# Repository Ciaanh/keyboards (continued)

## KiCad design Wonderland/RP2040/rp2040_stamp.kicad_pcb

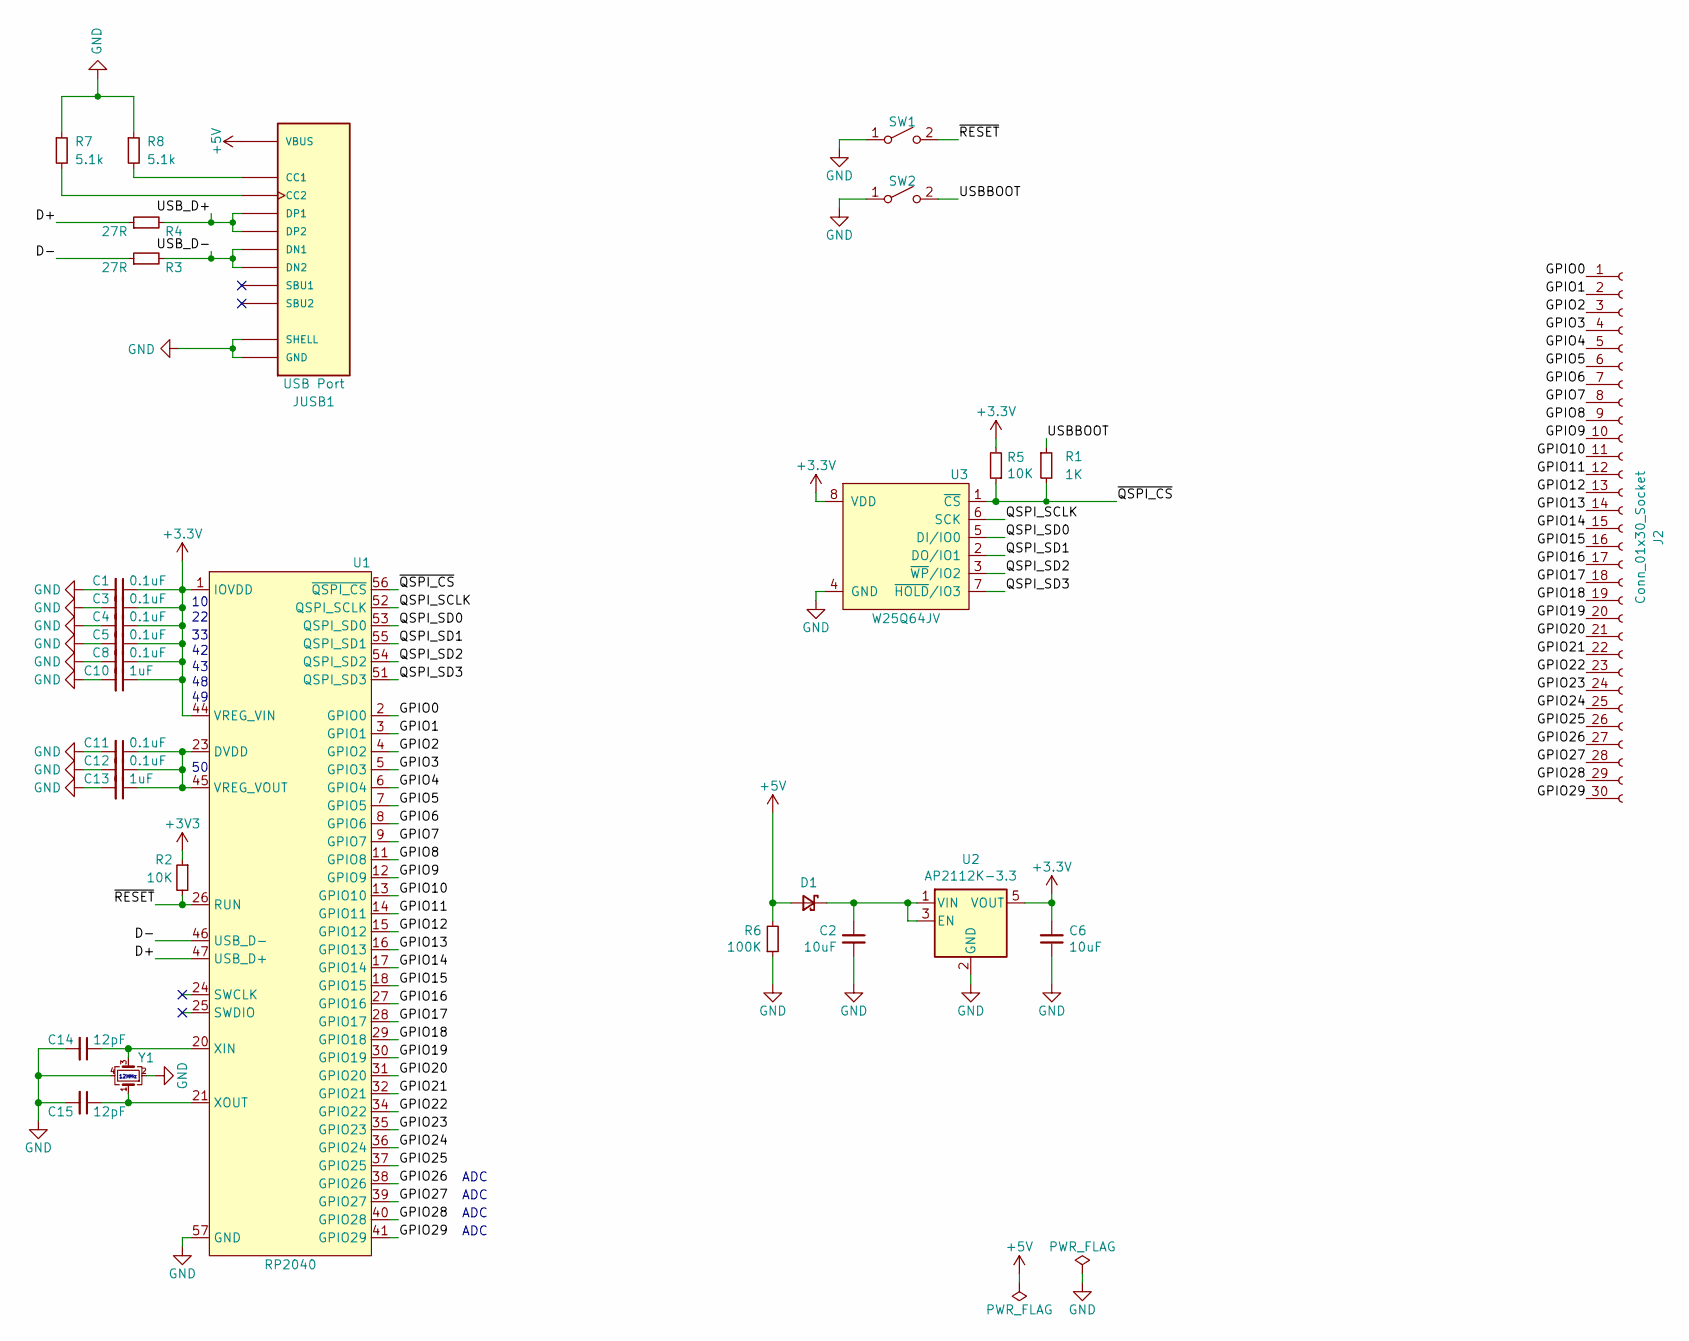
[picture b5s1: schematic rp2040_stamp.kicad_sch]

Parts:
C1, C3, C4, C5, C8, C11, C12: 0.1uF; C_0603_1608Metric
C2, C6: 10uF; C_0603_1608Metric
C10, C13: 1uF; C_0603_1608Metric
C14, C15: 12pF; C_0603_1608Metric
D1: D_Schottky_Small; D_SOD-323; LCSC C114023
J2: Conn_01x30_Socket; PinHeader_1x30_P2.54mm_Vertical
JUSB1: USB Port; GCT_USB4085-GF-A_REVA4; PARTREV A4
R1: 1K; R_0603_1608Metric
R2, R5: 10K; R_0603_1608Metric
R3, R4: 27R; R_0603_1608Metric
R6: 100K; R_0603_1608Metric
R7, R8: 5.1k; R_0603_1608Metric
SW1, SW2: SW_RESET; SW_SPST_B3U-1000P
U1: RP2040; QFN-56_EP_7x7_Pitch0.4mm
U2: AP2112K-3.3; SOT-23-5; LCSC C51118
U3: W25Q64JV; WSON-8-1EP_6x5mm_P1.27mm_EP3.4x4mm
Y1: XYDBPCNANF-12MHZ; Crystal_SMD_2520-4Pin_2.5x2.0mm; LCSC C521567

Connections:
+5V: D1.2 (A), JUSB1.A4 (VBUS), JUSB1.A9 (VBUS), JUSB1.B4 (VBUS), JUSB1.B9 (VBUS), R6.2
/D+: R4.1, U1.47 (USB_D+)
/D-: R3.1, U1.46 (USB_D-)
/GPIO0: J2.1, U1.2 (GPIO0)
/GPIO1: J2.2, U1.3 (GPIO1)
/GPIO2: J2.3, U1.4 (GPIO2)
/GPIO3: J2.4, U1.5 (GPIO3)
/GPIO4: J2.5, U1.6 (GPIO4)
/GPIO5: J2.6, U1.7 (GPIO5)
/GPIO6: J2.7, U1.8 (GPIO6)
/GPIO7: J2.8, U1.9 (GPIO7)
/GPIO8: J2.9, U1.11 (GPIO8)
/GPIO9: J2.10, U1.12 (GPIO9)
/GPIO10: J2.11, U1.13 (GPIO10)
/GPIO11: J2.12, U1.14 (GPIO11)
/GPIO12: J2.13, U1.15 (GPIO12)
/GPIO13: J2.14, U1.16 (GPIO13)
/GPIO14: J2.15, U1.17 (GPIO14)
/GPIO15: J2.16, U1.18 (GPIO15)
/GPIO16: J2.17, U1.27 (GPIO16)
/GPIO17: J2.18, U1.28 (GPIO17)
/GPIO18: J2.19, U1.29 (GPIO18)
/GPIO19: J2.20, U1.30 (GPIO19)
/GPIO20: J2.21, U1.31 (GPIO20)
/GPIO21: J2.22, U1.32 (GPIO21)
/GPIO22: J2.23, U1.34 (GPIO22)
/GPIO23: J2.24, U1.35 (GPIO23)
/GPIO24: J2.25, U1.36 (GPIO24)
/GPIO25: J2.26, U1.37 (GPIO25)
/GPIO26: J2.27, U1.38 (GPIO26)
/GPIO27: J2.28, U1.39 (GPIO27)
/GPIO28: J2.29, U1.40 (GPIO28)
/GPIO29: J2.30, U1.41 (GPIO29)
/QSPI_SCLK: U1.52 (QSPI_SCLK), U3.6 (SCK)
/QSPI_SD0: U1.53 (QSPI_SD0), U3.5 (DI/IO0)
/QSPI_SD1: U1.55 (QSPI_SD1), U3.2 (DO/IO1)
/QSPI_SD2: U1.54 (QSPI_SD2), U3.3 (~WP/IO2)
/QSPI_SD3: U1.51 (QSPI_SD3), U3.7 (~HOLD/IO3)
/USBBOOT: R1.1, SW2.2 (B)
/USB_D+: JUSB1.A6 (DP1), JUSB1.B6 (DP2), R4.2
/USB_D-: JUSB1.A7 (DN1), JUSB1.B7 (DN2), R3.2
/~QSPI_CS: R1.2, R5.1, U1.56 (~QSPI_CS), U3.1 (~CS)
/~RESET: R2.2, SW1.2 (B), U1.26 (RUN)
GND: C1.2, C2.2, C3.2, C4.2, C5.2, C6.1, C8.2, C10.2, C11.2, C12.2, C13.2, C14.2, C15.2, JUSB1.A1 (GND), JUSB1.A12 (GND), JUSB1.B1 (GND), JUSB1.B12 (GND), JUSB1.P1 (SHELL), JUSB1.P2 (SHELL), JUSB1.P3 (SHELL), JUSB1.P4 (SHELL), R6.1, R7.1, R8.1, SW1.1 (A), SW2.1 (A), U1.19 (TESTEN), U1.57 (GND), U2.2 (GND), U3.4 (GND), U3.9 (GND), Y1.2, Y1.4
unnamed: C2.1, D1.1 (K), U2.1 (VIN), U2.3 (EN)
unnamed: JUSB1.A5 (CC1), R8.2
unnamed: JUSB1.B5 (CC2), R7.2
unnamed: C11.1, C12.1, C13.1, U1.23 (DVDD), U1.45 (VREG_VOUT), U1.50 (DVDD)
unnamed: C14.1, U1.20 (XIN), Y1.3
unnamed: C15.1, U1.21 (XOUT), Y1.1

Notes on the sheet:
ADC
12MHz

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
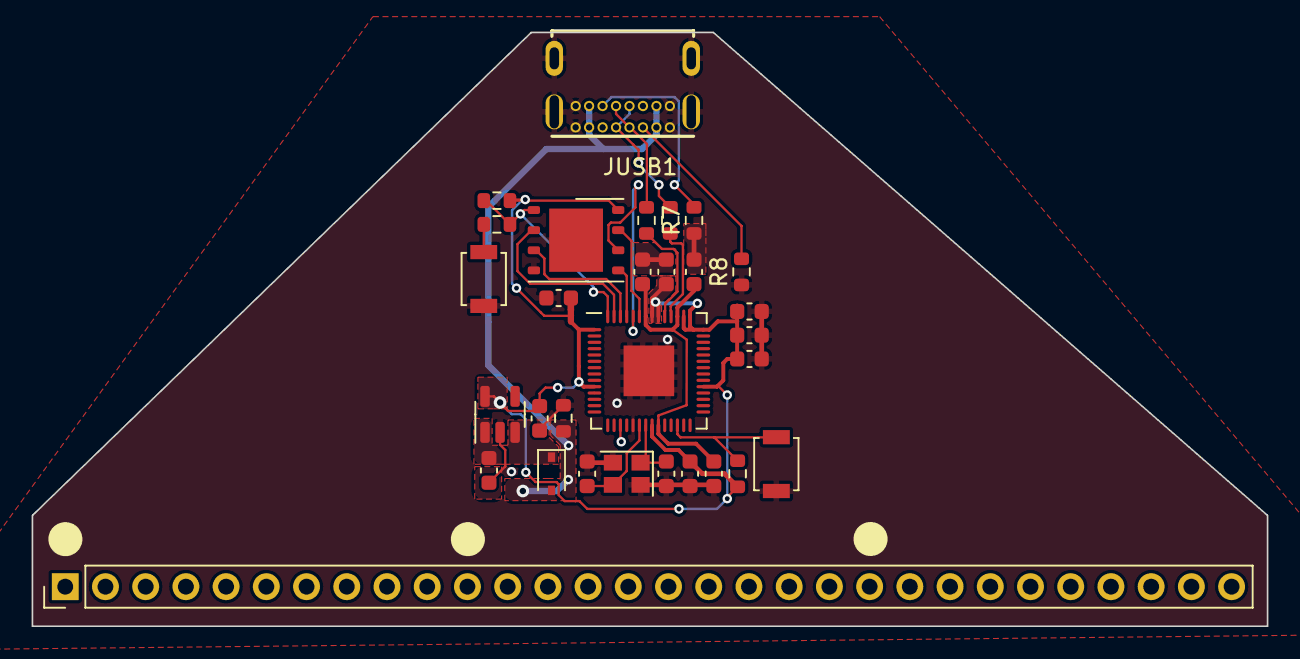
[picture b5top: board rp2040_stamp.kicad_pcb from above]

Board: 2 copper layers, 78.0 x 37.5 mm, 30 parts (0 on the bottom side), 51 nets.

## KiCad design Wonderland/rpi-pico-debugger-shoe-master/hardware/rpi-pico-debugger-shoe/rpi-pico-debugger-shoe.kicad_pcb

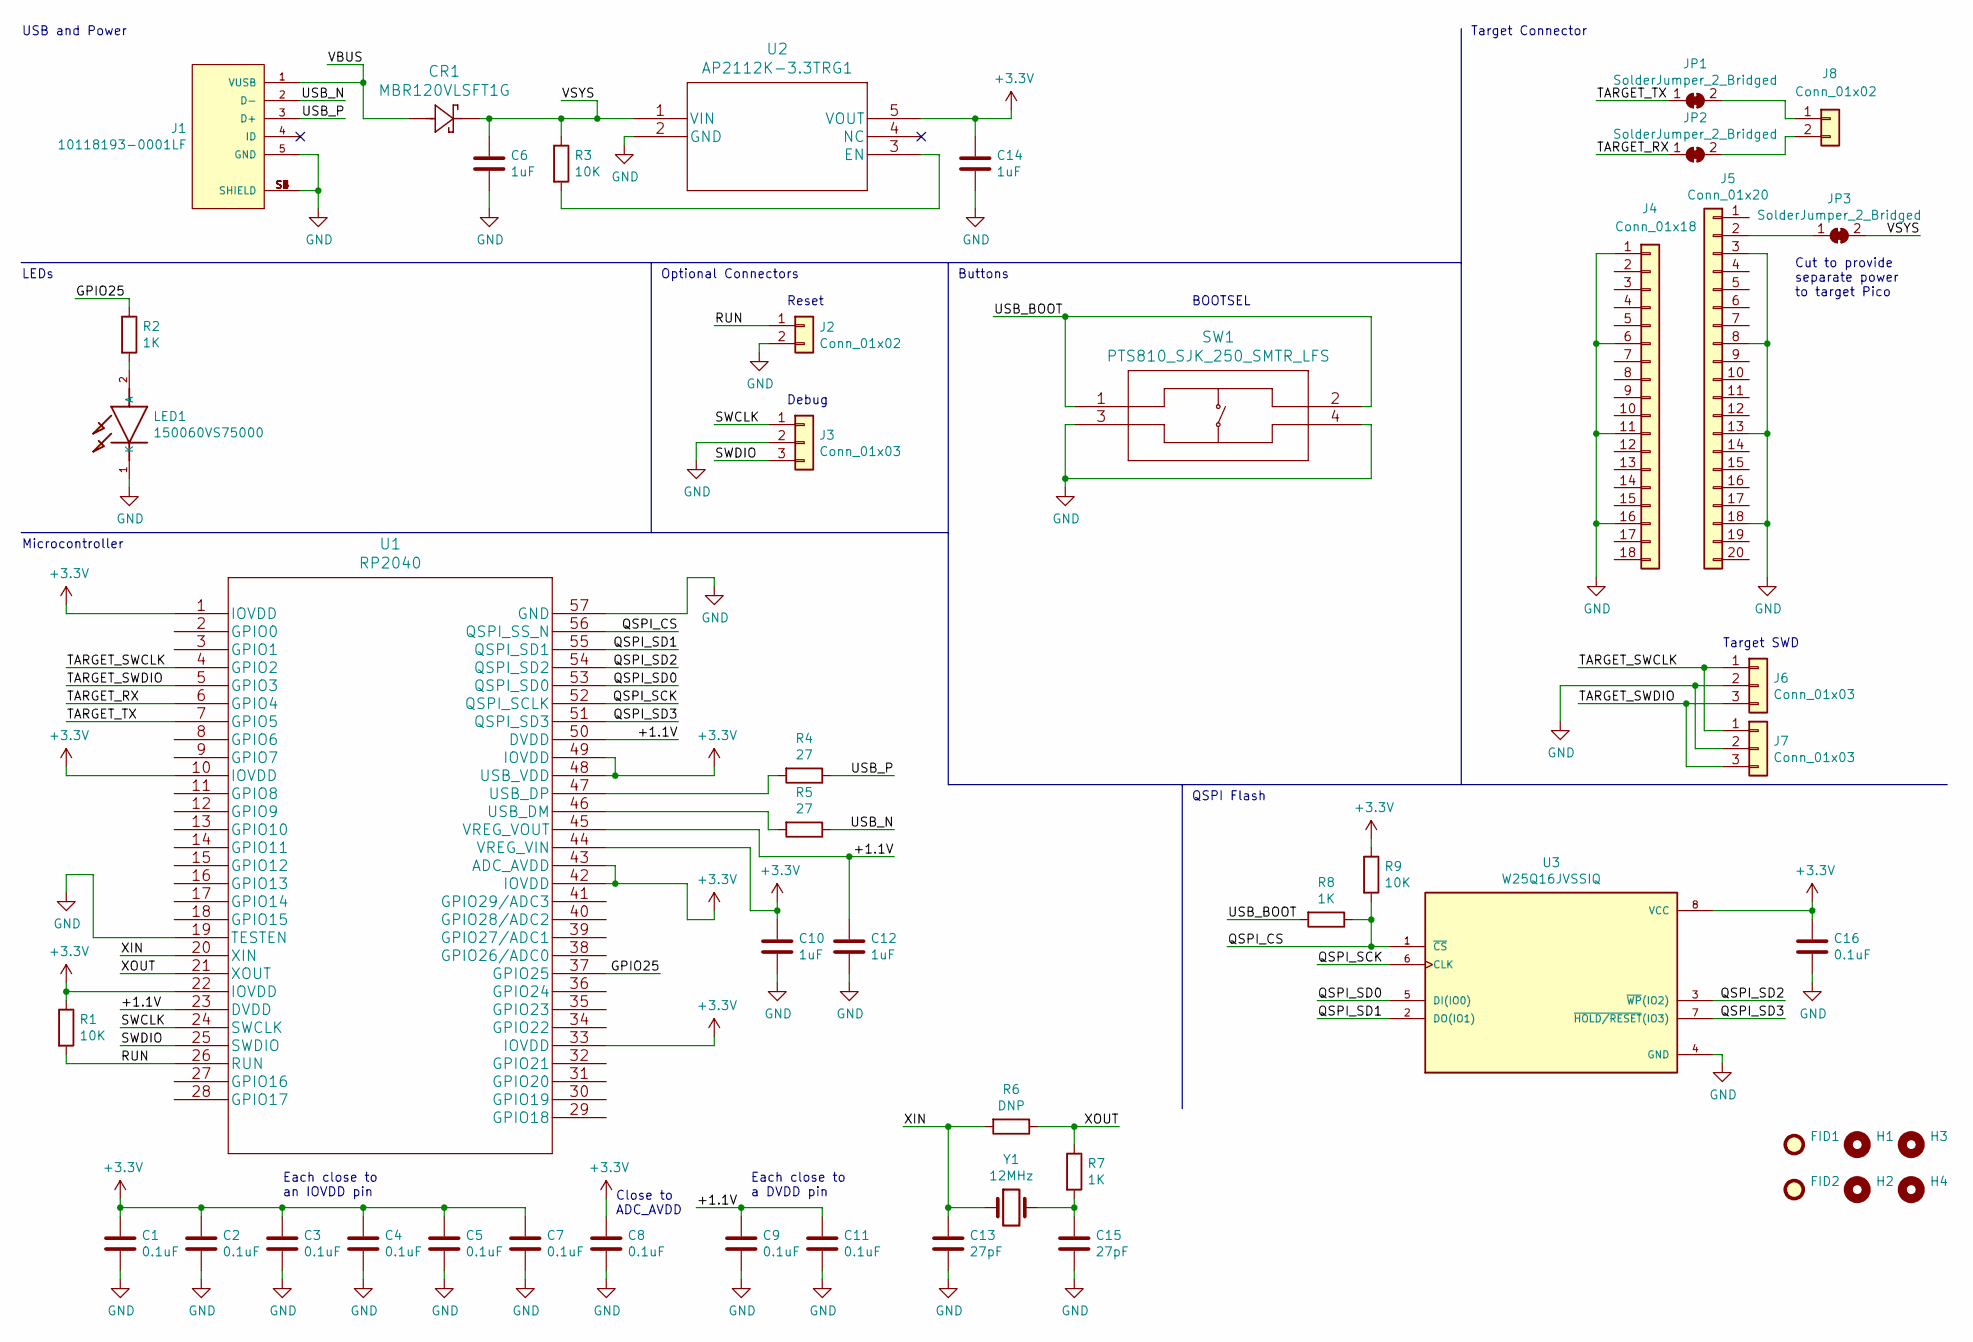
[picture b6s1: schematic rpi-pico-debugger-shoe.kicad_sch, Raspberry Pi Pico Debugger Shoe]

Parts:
C1, C2, C3, C4, C5, C7, C8, C9, C11, C16: 0.1uF; C_0603_1608Metric_Pad1.08x0.95mm_HandSolder; Digi-Key_PN 311-1344-1-ND
C6, C10, C12, C14: 1uF; C_0603_1608Metric_Pad1.08x0.95mm_HandSolder; Digi-Key_PN 1276-6524-1-ND
C13, C15: 27pF; C_0603_1608Metric_Pad1.08x0.95mm_HandSolder; Digi-Key_PN 311-1063-1-ND
CR1: MBR120VLSFT1G; Digi-Key_PN MBR120VLSFT1GOSCT-ND
FID1, FID2: Fiducial; Fiducial_1mm_Mask2mm
H1, H2, H3, H4: MountingHole; MountingHole_2.1mm
J1: 10118193-0001LF; FCI_10118193-0001LF_no-slot; Digi-Key_PN 609-4616-1-ND
J2: Conn_01x02; PinHeader_1x02_P2.54mm_Vertical_no-silk
J3, J6: Conn_01x03; PinHeader_1x03_P2.54mm_Vertical_no-silk
J4: Conn_01x18; PinHeader_1x18_P2.54mm_Vertical_no-silk; Digi-Key_PN 1988-1035-ND
J5: Conn_01x20; PinHeader_1x20_P2.54mm_Vertical_no-silk; Digi-Key_PN 1988-1136-ND
J7: Conn_01x03; PinHeader_1x03_P2.54mm_Vertical_no-silk; Digi-Key_PN S7036-ND
J8: Conn_01x02; PinHeader_1x02_P2.54mm_Vertical_no-silk; Digi-Key_PN S7035-ND
JP1, JP2, JP3: SolderJumper_2_Bridged; SolderJumper-2_P1.3mm_Bridged_RoundedPad1.0x1.5mm
LED1: 150060VS75000; LEDC1608X80N; MOUSER_PART_NUMBER 710-150060VS75000
R1, R3, R9: 10K; R_0603_1608Metric_Pad0.98x0.95mm_HandSolder; Digi-Key_PN 311-10KGRCT-ND
R2, R7, R8: 1K; R_0603_1608Metric_Pad0.98x0.95mm_HandSolder; Digi-Key_PN 311-1.00KHRCT-ND
R4, R5: 27; R_0603_1608Metric_Pad0.98x0.95mm_HandSolder; Digi-Key_PN 311-27.0HRCT-ND
R6: DNP; R_0603_1608Metric_Pad0.98x0.95mm_HandSolder
SW1: PTS810_SJK_250_SMTR_LFS; PTS810 SJK 250 SMTR LFS; Digi-Key_PN CKN10503CT-ND
U1: RP2040; Digi-Key_PN TBD
U2: AP2112K-3.3TRG1; Digi-Key_PN AP2112K-3.3TRG1DICT-ND
U3: W25Q16JVSSIQ; SOIC127P790X216-8N; Digi-Key_PN 256-W25Q16JVSSIM-ND
Y1: 12MHz; ABLS7M2-16.000MHZ-D-2Y-T; Digi-Key_PN 535-13415-1-ND

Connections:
+3V3: C1.1, C2.1, C3.1, C4.1, C5.1, C7.1, C8.1, C10.1, C14.1, C16.1, R1.1, R9.1, U1.1 (IOVDD), U1.10 (IOVDD), U1.22 (IOVDD), U1.33 (IOVDD), U1.42 (IOVDD), U1.43 (ADC_AVDD), U1.44 (VREG_VIN), U1.48 (USB_VDD), U1.49 (IOVDD), U2.5 (VOUT), U3.8 (VCC)
/+1.1V: C9.1, C11.1, C12.1, U1.23 (DVDD), U1.45 (VREG_VOUT), U1.50 (DVDD)
/GPIO25: R2.1, U1.37 (GPIO25)
/QSPI_CS: R8.1, R9.2, U1.56 (QSPI_SS_N), U3.1 (~CS)
/QSPI_SCK: U1.52 (QSPI_SCLK), U3.6 (CLK)
/QSPI_SD0: U1.53 (QSPI_SD0), U3.5 (DI(IO0))
/QSPI_SD1: U1.55 (QSPI_SD1), U3.2 (DO(IO1))
/QSPI_SD2: U1.54 (QSPI_SD2), U3.3 (~WP(IO2))
/QSPI_SD3: U1.51 (QSPI_SD3), U3.7 (~HOLD/RESET(IO3))
/RUN: J2.1, R1.2, U1.26 (RUN)
/SWCLK: J3.1, U1.24 (SWCLK)
/SWDIO: J3.3, U1.25 (SWDIO)
/TARGET_RX: JP2.1 (A), U1.6 (GPIO4)
/TARGET_SWCLK: J6.1, J7.1, U1.4 (GPIO2)
/TARGET_SWDIO: J6.3, J7.3, U1.5 (GPIO3)
/TARGET_TX: JP1.1 (A), U1.7 (GPIO5)
/USB_BOOT: R8.2, SW1.1, SW1.2
/USB_N: J1.2 (D-), R5.1
/USB_P: J1.3 (D+), R4.1
/VBUS: CR1.2, J1.1 (VUSB)
/VSYS: C6.1, CR1.1, JP3.2 (B), R3.1, U2.1 (VIN)
/XIN: C13.1, R6.2, U1.20 (XIN), Y1.1
/XOUT: R6.1, R7.1, U1.21 (XOUT)
GND: C1.2, C2.2, C3.2, C4.2, C5.2, C6.2, C7.2, C8.2, C9.2, C10.2, C11.2, C12.2, C13.2, C14.2, C15.2, C16.2, J1.5 (GND), J1.S1 (SHIELD), J1.S2 (SHIELD), J1.S3 (SHIELD), J1.S4 (SHIELD), J1.S5 (SHIELD), J1.S6 (SHIELD), J2.2, J3.2, J4.1, J4.6, J4.11, J4.16, J5.3, J5.8, J5.13, J5.18, J6.2, J7.2, LED1.1 (K), SW1.3, SW1.4, U1.19 (TESTEN), U1.57 (GND), U2.2 (GND), U3.4 (GND)
unnamed: C15.1, R7.2, Y1.2
unnamed: J5.2, JP3.1 (A)
unnamed: J8.1, JP1.2 (B)
unnamed: J8.2, JP2.2 (B)
unnamed: LED1.2 (A), R2.2
unnamed: R3.2, U2.3 (EN)
unnamed: R4.2, U1.47 (USB_DP)
unnamed: R5.2, U1.46 (USB_DM)

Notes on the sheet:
Reset
Buttons
Target Connector
QSPI Flash
Microcontroller
Target SWD
BOOTSEL
Cut to provide separate power to target Pico
Debug
USB and Power
Optional Connectors
LEDs
Each close to a DVDD pin
Each close to an IOVDD pin
Close to ADC_AVDD

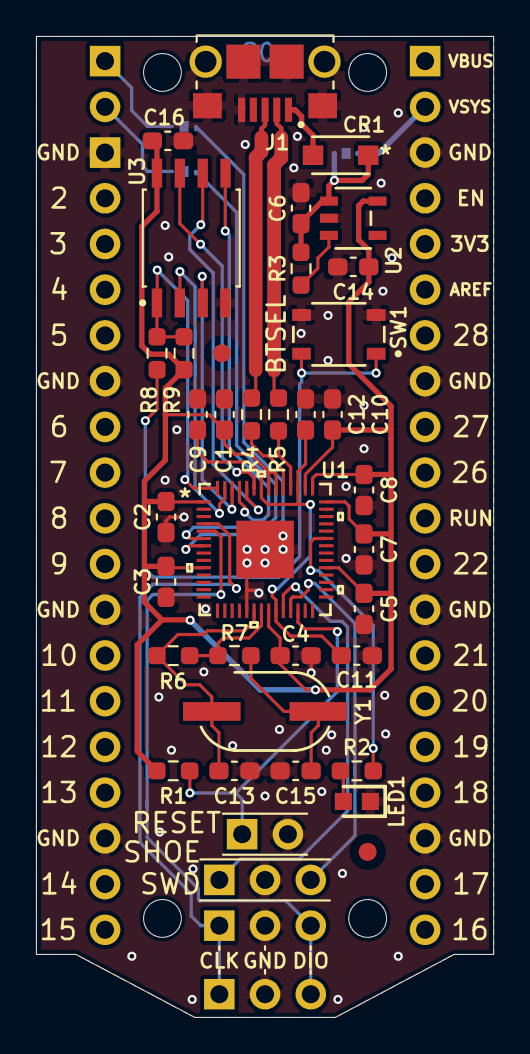
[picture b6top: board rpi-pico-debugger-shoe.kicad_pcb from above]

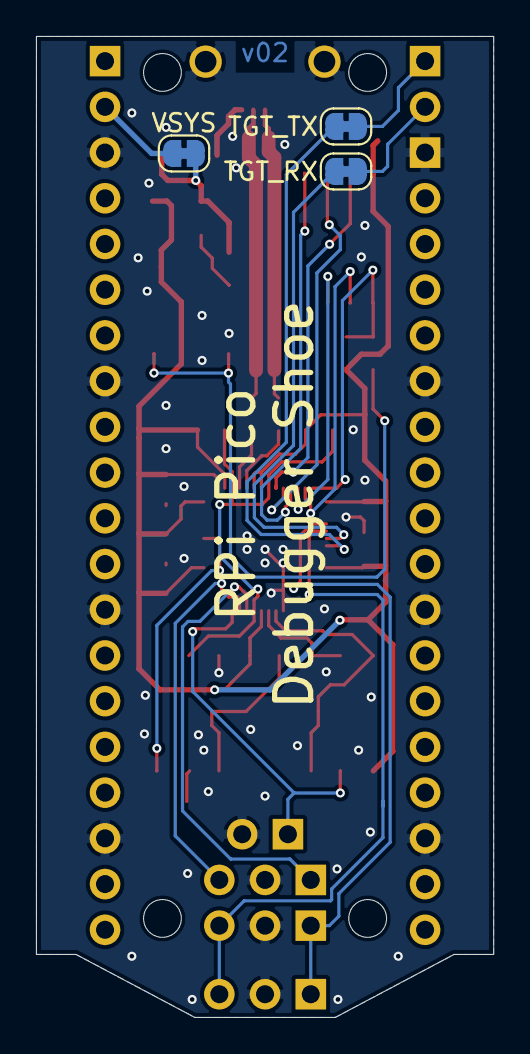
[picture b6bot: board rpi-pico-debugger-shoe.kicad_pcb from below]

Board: 2 copper layers, 25.4 x 54.5 mm, 49 parts (3 on the bottom side), 32 nets.

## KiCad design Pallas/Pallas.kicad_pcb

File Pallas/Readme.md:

Pallas: one of the names of Athena, goddess of wisdom, war and craftsmanship.

This keyboard was inspired by the famous Alice keyboard.
The main issue I found with the layout of the Alice keyboard is that despite being "ergonomic" the two halves were too close for me. The result is the twelve keys pad at the center which filled the gap between the left and right part while providing function keys, num pad or macro keys.

While working on the PCB I found out the work of @tomsaleeba with the Ergoslab [https://github.com/tomsaleeba/ergoslab] and especially his idea of using one PCB file in Kicad with a Python script to generate the bas, middle and top PCBs for a complete PCB case design.

# Layout

# Build guide

I am still working on the prototype but rev 0.3 should be really close to a final version.

Minimum required components

- 75 switch MX compatible
- 75 1N4148 diodes (through hole or SMD)
- 1 Elite-C  ( [US](https://keeb.io/collections/frontpage/products/elite-c-low-profile-version-usb-c-pro-micro-replacement-atmega32u4) [EU](https://splitkb.com/products/elite-c-low-profile-rev4-microcontroller) )

Optional

- 1 switch for reset ([MJTP1117](https://fr.farnell.com/apem/mjtp1117/tactile-sw-spst-0-05a-12vdc-th/dp/2858318?ost=mjtp1117))

For RGB

- 4 WS2812B RGB LEDs
OR
- 1 RGB LEDs Strip ( SK6812/WS2812B compatible )

For switch LED

- 75 3mm LED
- 75 470 Ω resistors
- 1 1 kΩ resistor
- 1 mosfet SOT-23 ([IRLML6344TRPBF](https://fr.farnell.com/infineon/irlml6344trpbf/mosfet-canal-n-30v-6-3a-sot23/dp/1857299))

For OLED

- 1 128x64 4 pins OLED Display [SSD1306](https://splitkb.com/products/oled-display)
- 2 4.7 kΩ resistors

# Script

Some changes were made to @tomsaleeba's script.

Affect module to a PCB:
I decided to use another solution to define to which PCB a module should be drawn, for a given module we can set is its reference the PCB layer "Base", "Middle" or "Top".
This allow us to place elements on top and base PCB and not on the middle layer for example.

Back plate design:
It happens that we want to have a special design for the backplate of the board.
To ease this I decided to use the "Eco2.User" in wich all segment will better rendered on the "B.SilkS" of the "Base" PCB.

Self defined footprints:
One the main issue I had was that on the Ergoslab the cutout for the switch were drawn on the board "Eco1.User". But I have a lot of switch, some have stabilizer, and if I ever wanted to move switchs I would have to move all the corresponding cutout.
The solution I found was to draw the cutout directly in the "Eco1.User" of the switch footprint and then move them to the "Edge.Cuts" layer of the "Top" PCB. Check the *extract_module_cutout* and *clone_edge_to_board* to find how it works.

I'm working on Windows using Windows terminal and WSL so the command looks like :
    ``python3 ./generate_pcbs.py``

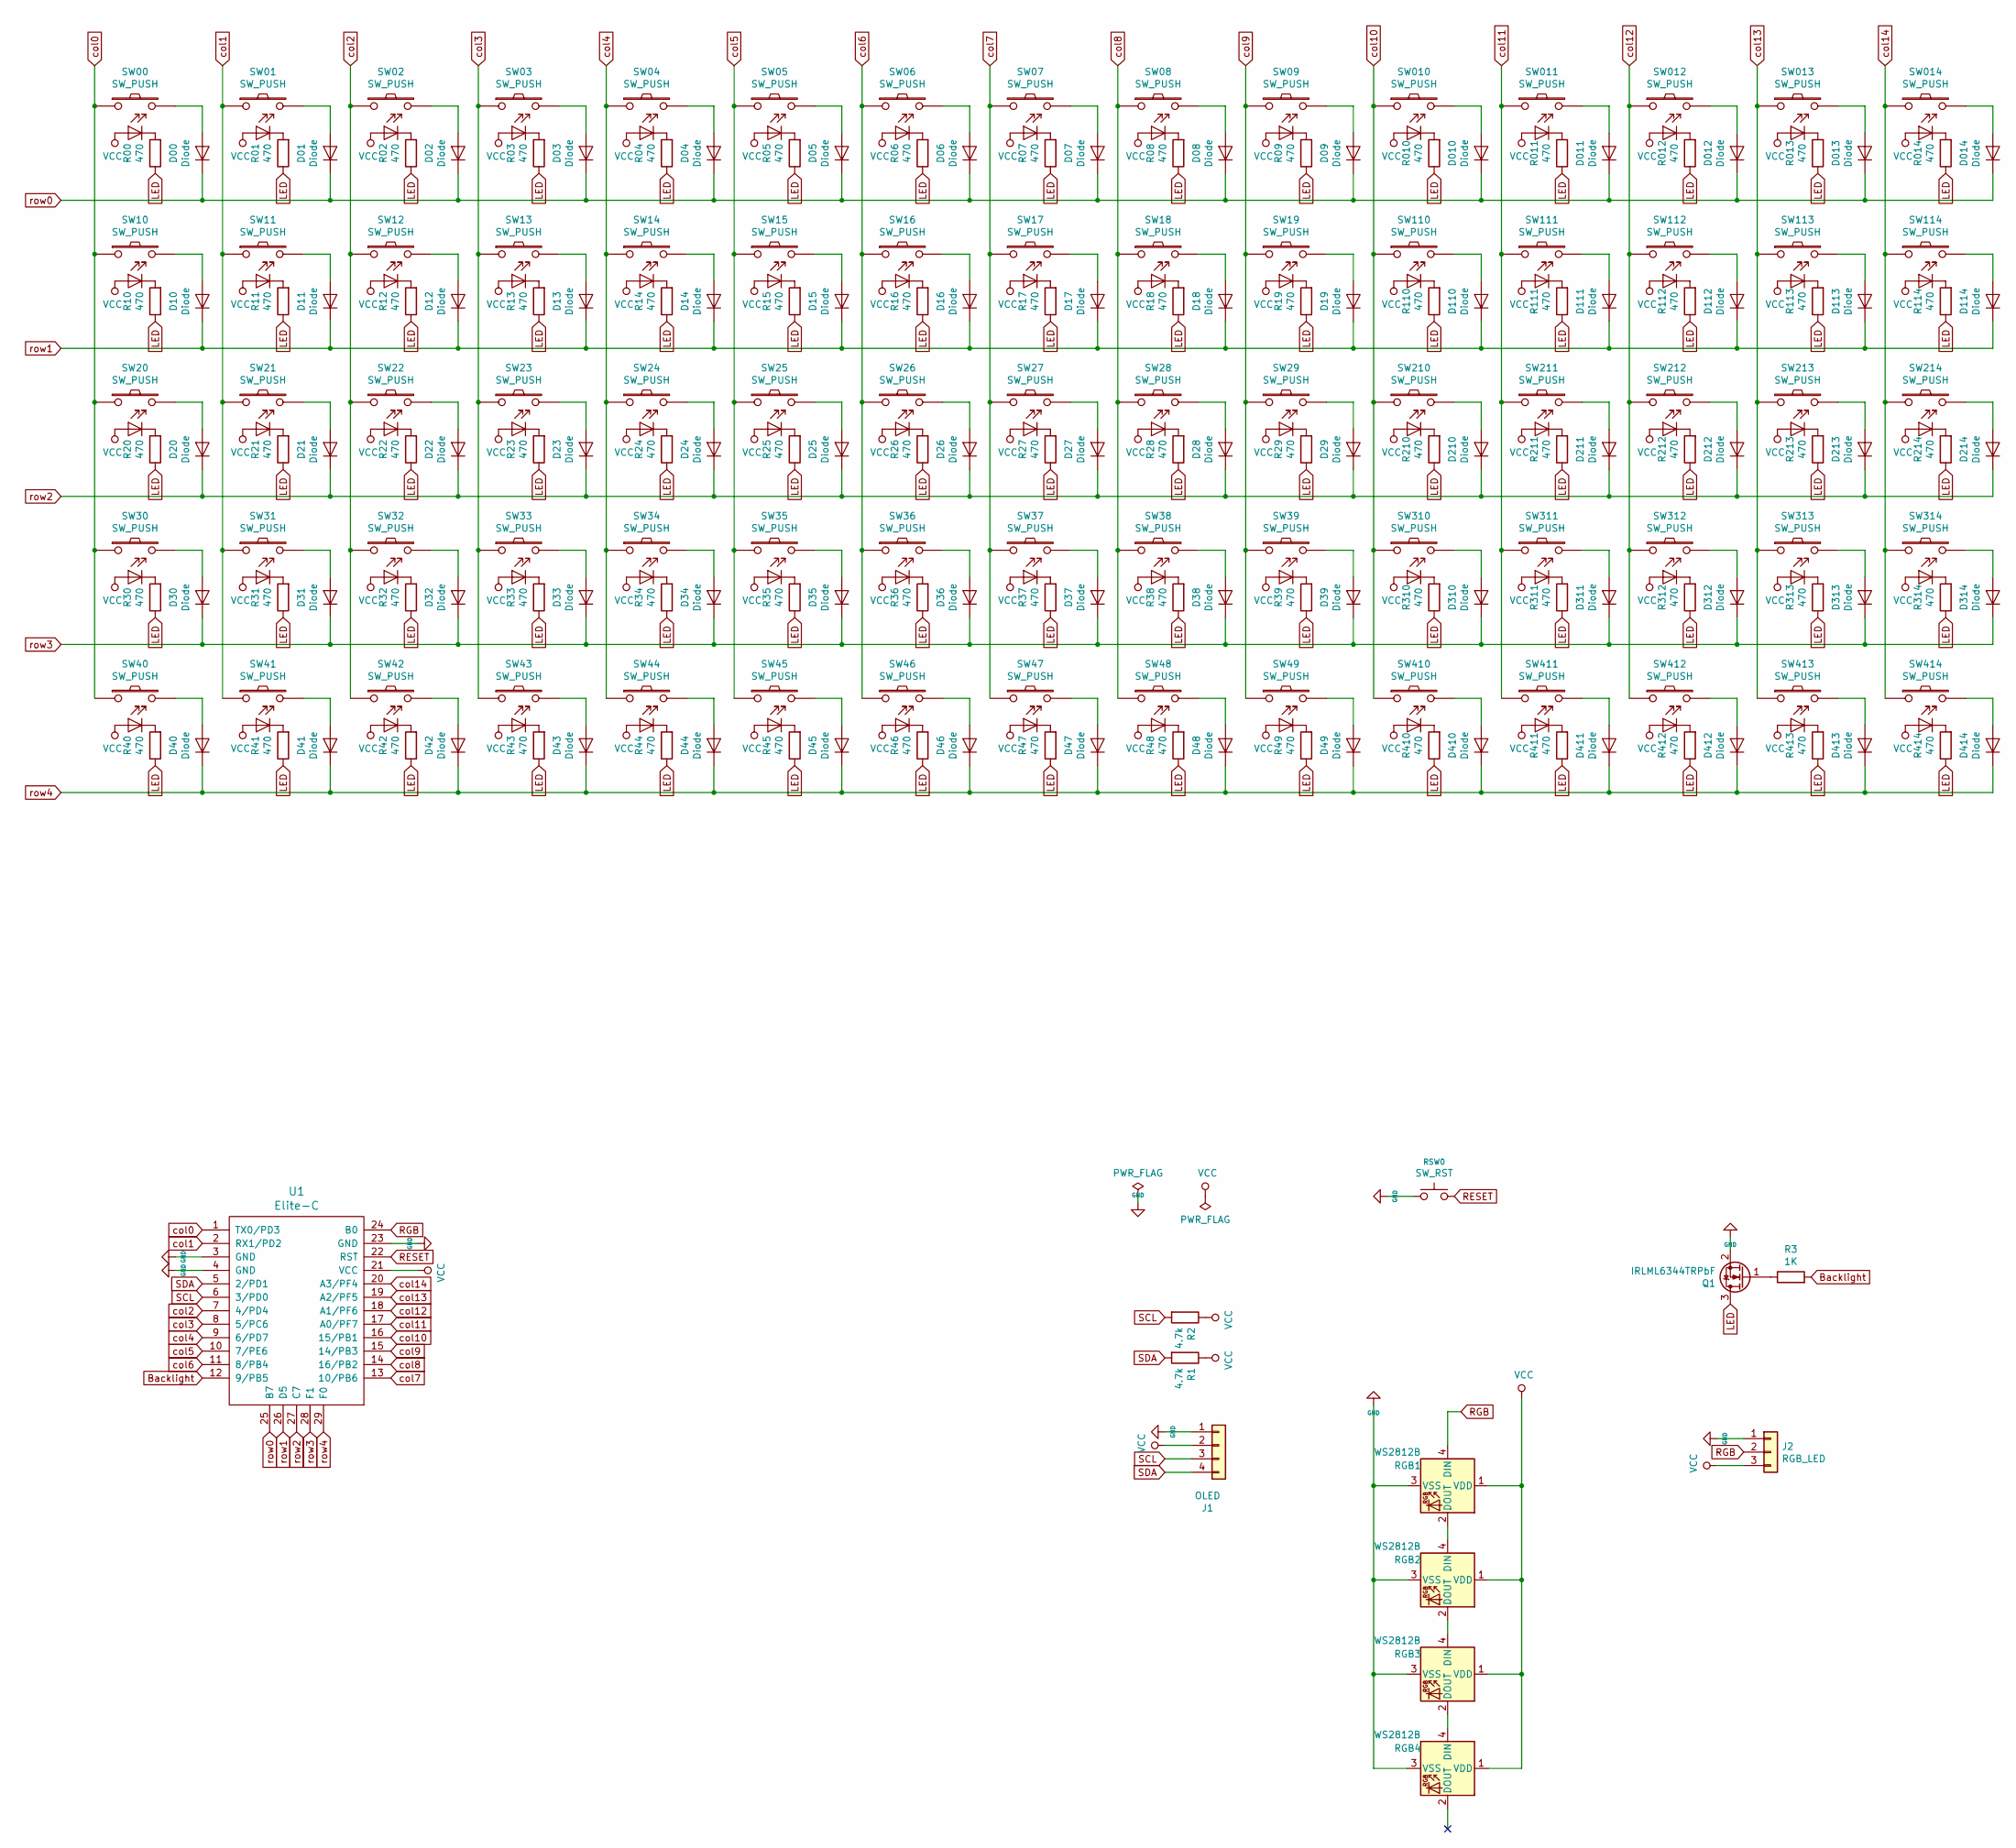
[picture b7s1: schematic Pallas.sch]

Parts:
D00, D01, D02, D03, D04, D05, D06, D07, D08, D09, D010, D10, D11, D011, D12, D012, D13, D013, D14, D014, D15, D16, D17, D18, D19, D20, D21, D22, D23, D24, D25, D26, D27, D28, D29, D30, D31, D32, D33, D34, D35, D36, D37, D38, D39, D40, D41, D42, D43, D44, D45, D46, D47, D48, D49, D110, D111, D112, D113, D114, D210, D211, D212, D213, D214, D310, D311, D312, D313, D314, D410, D411, D412, D413, D414: Diode; Diode_SMD_THT
J1: OLED; OLED_128x64_I2C
J2: RGB_LED; conn_3pins
Q1: IRLML6344TRPbF; SOT23-3_HSOL_Back
R00, R01, R02, R03, R04, R05, R06, R07, R08, R09, R010, R10, R11, R011, R12, R012, R13, R013, R14, R014, R15, R16, R17, R18, R19, R20, R21, R22, R23, R24, R25, R26, R27, R28, R29, R30, R31, R32, R33, R34, R35, R36, R37, R38, R39, R40, R41, R42, R43, R44, R45, R46, R47, R48, R49, R110, R111, R112, R113, R114, R210, R211, R212, R213, R214, R310, R311, R312, R313, R314, R410, R411, R412, R413, R414: 470; Resistors_SMD_THT
R1, R2: 4.7k; Resistors_SMD_THT
R3: 1K; Resistors_SMD_THT
RGB1, RGB2, RGB3, RGB4: WS2812B; WS2812B_Front
RSW0: SW_RST
SW00, SW01, SW02, SW03, SW04, SW05, SW06, SW07, SW08, SW09, SW010, SW11, SW011, SW12, SW012, SW13, SW013, SW14, SW014, SW15, SW16, SW17, SW18, SW19, SW21, SW22, SW23, SW24, SW25, SW26, SW27, SW28, SW29, SW31, SW32, SW33, SW34, SW35, SW36, SW37, SW38, SW39, SW43, SW46, SW47, SW48, SW49, SW110, SW111, SW112, SW113, SW114, SW210, SW211, SW212, SW213, SW310, SW311, SW312, SW313, SW410: SW_PUSH; SW_Cherry_MX_1.00u_PCB
SW10: SW_PUSH; SW_Cherry_MX_1.50u_PCB
SW20, SW314: SW_PUSH; SW_Cherry_MX_1.75u_PCB
SW30: SW_PUSH; SW_Cherry_MX_2.25u_PCB
SW40, SW41, SW42, SW45, SW411, SW413, SW414: SW_PUSH; SW_Cherry_MX_1.25u_PCB
SW44: SW_PUSH; SW_Cherry_MX_2.00u_PCB
SW214: SW_PUSH; SW_Cherry_MX_2.25u_ISO_PCB
SW412: SW_PUSH; SW_Cherry_MX_2.75u_PCB
U1: Elite-C; Elite-C-castellated-29pin-holes

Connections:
Backlight: R3.2, U1.12 (9/PB5)
GND: J1.1, J2.1, Q1.2 (S), RGB1.3 (VSS), RGB2.3 (VSS), RGB3.3 (VSS), RGB4.3 (VSS), RSW0.1, U1.3 (GND), U1.4 (GND), U1.23 (GND)
LED: Q1.3 (D), R00.1, R01.1, R02.1, R03.1, R04.1, R05.1, R06.1, R07.1, R08.1, R09.1, R10.1, R010.1, R11.1, R011.1, R012.1, R12.1, R13.1, R013.1, R014.1, R14.1, R15.1, R16.1, R17.1, R18.1, R19.1, R20.1, R21.1, R22.1, R23.1, R24.1, R25.1, R26.1, R27.1, R28.1, R29.1, R30.1, R31.1, R32.1, R33.1, R34.1, R35.1, R36.1, R37.1, R38.1, R39.1, R40.1, R41.1, R42.1, R43.1, R44.1, R45.1, R46.1, R47.1, R48.1, R49.1, R110.1, R111.1, R112.1, R113.1, R114.1, R210.1, R211.1, R212.1, R213.1, R214.1, R310.1, R311.1, R312.1, R313.1, R314.1, R410.1, R411.1, R412.1, R413.1, R414.1
unnamed: D00.2 (A), SW00.2
unnamed: D01.2 (A), SW01.2
unnamed: D02.2 (A), SW02.2
unnamed: D03.2 (A), SW03.2
unnamed: D04.2 (A), SW04.2
unnamed: D05.2 (A), SW05.2
unnamed: D06.2 (A), SW06.2
unnamed: D07.2 (A), SW07.2
unnamed: D08.2 (A), SW08.2
unnamed: D09.2 (A), SW09.2
unnamed: D010.2 (A), SW010.2
unnamed: D10.2 (A), SW10.2
unnamed: D011.2 (A), SW011.2
unnamed: D11.2 (A), SW11.2
unnamed: D012.2 (A), SW012.2
unnamed: D12.2 (A), SW12.2
unnamed: D013.2 (A), SW013.2
unnamed: D13.2 (A), SW13.2
unnamed: D014.2 (A), SW014.2
unnamed: D14.2 (A), SW14.2
unnamed: D15.2 (A), SW15.2
unnamed: D16.2 (A), SW16.2
unnamed: D17.2 (A), SW17.2
unnamed: D18.2 (A), SW18.2
unnamed: D19.2 (A), SW19.2
unnamed: D20.2 (A), SW20.2
unnamed: D21.2 (A), SW21.2
unnamed: D22.2 (A), SW22.2
unnamed: D23.2 (A), SW23.2
unnamed: D24.2 (A), SW24.2
unnamed: D25.2 (A), SW25.2
unnamed: D26.2 (A), SW26.2
unnamed: D27.2 (A), SW27.2
unnamed: D28.2 (A), SW28.2
unnamed: D29.2 (A), SW29.2
unnamed: D30.2 (A), SW30.2
unnamed: D31.2 (A), SW31.2
unnamed: D32.2 (A), SW32.2
unnamed: D33.2 (A), SW33.2
unnamed: D34.2 (A), SW34.2
unnamed: D35.2 (A), SW35.2
unnamed: D36.2 (A), SW36.2
unnamed: D37.2 (A), SW37.2
unnamed: D38.2 (A), SW38.2
unnamed: D39.2 (A), SW39.2
unnamed: D40.2 (A), SW40.2
unnamed: D41.2 (A), SW41.2
unnamed: D42.2 (A), SW42.2
unnamed: D43.2 (A), SW43.2
unnamed: D44.2 (A), SW44.2
unnamed: D45.2 (A), SW45.2
unnamed: D46.2 (A), SW46.2
unnamed: D47.2 (A), SW47.2
unnamed: D48.2 (A), SW48.2
unnamed: D49.2 (A), SW49.2
unnamed: D110.2 (A), SW110.2
unnamed: D111.2 (A), SW111.2
unnamed: D112.2 (A), SW112.2
unnamed: D113.2 (A), SW113.2
unnamed: D114.2 (A), SW114.2
unnamed: D210.2 (A), SW210.2
unnamed: D211.2 (A), SW211.2
unnamed: D212.2 (A), SW212.2
unnamed: D213.2 (A), SW213.2
unnamed: D214.2 (A), SW214.2
unnamed: D310.2 (A), SW310.2
unnamed: D311.2 (A), SW311.2
unnamed: D312.2 (A), SW312.2
unnamed: D313.2 (A), SW313.2
unnamed: D314.2 (A), SW314.2
unnamed: D410.2 (A), SW410.2
unnamed: D411.2 (A), SW411.2
unnamed: D412.2 (A), SW412.2
unnamed: D413.2 (A), SW413.2
unnamed: D414.2 (A), SW414.2
unnamed: Q1.1 (G), R3.1
unnamed: R00.2, SW00.4 (K)
unnamed: R01.2, SW01.4 (K)
unnamed: R02.2, SW02.4 (K)
unnamed: R03.2, SW03.4 (K)
unnamed: R04.2, SW04.4 (K)
unnamed: R05.2, SW05.4 (K)
unnamed: R06.2, SW06.4 (K)
unnamed: R07.2, SW07.4 (K)
unnamed: R08.2, SW08.4 (K)
unnamed: R09.2, SW09.4 (K)
unnamed: R010.2, SW010.4 (K)
unnamed: R10.2, SW10.4 (K)
unnamed: R011.2, SW011.4 (K)
unnamed: R11.2, SW11.4 (K)
unnamed: R012.2, SW012.4 (K)
unnamed: R12.2, SW12.4 (K)
unnamed: R013.2, SW013.4 (K)
unnamed: R13.2, SW13.4 (K)
unnamed: R014.2, SW014.4 (K)
unnamed: R14.2, SW14.4 (K)
unnamed: R15.2, SW15.4 (K)
unnamed: R16.2, SW16.4 (K)
unnamed: R17.2, SW17.4 (K)
unnamed: R18.2, SW18.4 (K)
unnamed: R19.2, SW19.4 (K)
unnamed: R20.2, SW20.4 (K)
unnamed: R21.2, SW21.4 (K)
unnamed: R22.2, SW22.4 (K)
unnamed: R23.2, SW23.4 (K)
unnamed: R24.2, SW24.4 (K)
unnamed: R25.2, SW25.4 (K)
unnamed: R26.2, SW26.4 (K)
unnamed: R27.2, SW27.4 (K)
unnamed: R28.2, SW28.4 (K)
unnamed: R29.2, SW29.4 (K)
unnamed: R30.2, SW30.4 (K)
unnamed: R31.2, SW31.4 (K)
unnamed: R32.2, SW32.4 (K)
unnamed: R33.2, SW33.4 (K)
unnamed: R34.2, SW34.4 (K)
unnamed: R35.2, SW35.4 (K)
unnamed: R36.2, SW36.4 (K)
unnamed: R37.2, SW37.4 (K)
unnamed: R38.2, SW38.4 (K)
unnamed: R39.2, SW39.4 (K)
unnamed: R40.2, SW40.4 (K)
unnamed: R41.2, SW41.4 (K)
unnamed: R42.2, SW42.4 (K)
unnamed: R43.2, SW43.4 (K)
unnamed: R44.2, SW44.4 (K)
unnamed: R45.2, SW45.4 (K)
unnamed: R46.2, SW46.4 (K)
unnamed: R47.2, SW47.4 (K)
unnamed: R48.2, SW48.4 (K)
unnamed: R49.2, SW49.4 (K)
unnamed: R110.2, SW110.4 (K)
unnamed: R111.2, SW111.4 (K)
unnamed: R112.2, SW112.4 (K)
unnamed: R113.2, SW113.4 (K)
unnamed: R114.2, SW114.4 (K)
unnamed: R210.2, SW210.4 (K)
unnamed: R211.2, SW211.4 (K)
unnamed: R212.2, SW212.4 (K)
unnamed: R213.2, SW213.4 (K)
unnamed: R214.2, SW214.4 (K)
unnamed: R310.2, SW310.4 (K)
unnamed: R311.2, SW311.4 (K)
unnamed: R312.2, SW312.4 (K)
unnamed: R313.2, SW313.4 (K)
unnamed: R314.2, SW314.4 (K)
unnamed: R410.2, SW410.4 (K)
unnamed: R411.2, SW411.4 (K)
unnamed: R412.2, SW412.4 (K)
unnamed: R413.2, SW413.4 (K)
unnamed: R414.2, SW414.4 (K)
unnamed: RGB1.2 (DOUT), RGB2.4 (DIN)
unnamed: RGB2.2 (DOUT), RGB3.4 (DIN)
unnamed: RGB3.2 (DOUT), RGB4.4 (DIN)
RESET: RSW0.2, U1.22 (RST)
RGB: J2.2, RGB1.4 (DIN), U1.24 (B0)
SCL: J1.3, R2.2, U1.6 (3/PD0)
SDA: J1.4, R1.2, U1.5 (2/PD1)
VCC: J1.2, J2.3, R1.1, R2.1, RGB1.1 (VDD), RGB2.1 (VDD), RGB3.1 (VDD), RGB4.1 (VDD), SW00.3 (A), SW01.3 (A), SW02.3 (A), SW03.3 (A), SW04.3 (A), SW05.3 (A), SW06.3 (A), SW07.3 (A), SW08.3 (A), SW09.3 (A), SW010.3 (A), SW10.3 (A), SW011.3 (A), SW11.3 (A), SW012.3 (A), SW12.3 (A), SW013.3 (A), SW13.3 (A), SW014.3 (A), SW14.3 (A), SW15.3 (A), SW16.3 (A), SW17.3 (A), SW18.3 (A), SW19.3 (A), SW20.3 (A), SW21.3 (A), SW22.3 (A), SW23.3 (A), SW24.3 (A), SW25.3 (A), SW26.3 (A), SW27.3 (A), SW28.3 (A), SW29.3 (A), SW30.3 (A), SW31.3 (A), SW32.3 (A), SW33.3 (A), SW34.3 (A), SW35.3 (A), SW36.3 (A), SW37.3 (A), SW38.3 (A), SW39.3 (A), SW40.3 (A), SW41.3 (A), SW42.3 (A), SW43.3 (A), SW44.3 (A), SW45.3 (A), SW46.3 (A), SW47.3 (A), SW48.3 (A), SW49.3 (A), SW110.3 (A), SW111.3 (A), SW112.3 (A), SW113.3 (A), SW114.3 (A), SW210.3 (A), SW211.3 (A), SW212.3 (A), SW213.3 (A), SW214.3 (A), SW310.3 (A), SW311.3 (A), SW312.3 (A), SW313.3 (A), SW314.3 (A), SW410.3 (A), SW411.3 (A), SW412.3 (A), SW413.3 (A), SW414.3 (A), U1.21 (VCC)
col0: SW00.1, SW10.1, SW20.1, SW30.1, SW40.1, U1.1 (TX0/PD3)
col1: SW01.1, SW11.1, SW21.1, SW31.1, SW41.1, U1.2 (RX1/PD2)
col2: SW02.1, SW12.1, SW22.1, SW32.1, SW42.1, U1.7 (4/PD4)
col3: SW03.1, SW13.1, SW23.1, SW33.1, SW43.1, U1.8 (5/PC6)
col4: SW04.1, SW14.1, SW24.1, SW34.1, SW44.1, U1.9 (6/PD7)
col5: SW05.1, SW15.1, SW25.1, SW35.1, SW45.1, U1.10 (7/PE6)
col6: SW06.1, SW16.1, SW26.1, SW36.1, SW46.1, U1.11 (8/PB4)
col7: SW07.1, SW17.1, SW27.1, SW37.1, SW47.1, U1.13 (10/PB6)
col8: SW08.1, SW18.1, SW28.1, SW38.1, SW48.1, U1.14 (16/PB2)
col9: SW09.1, SW19.1, SW29.1, SW39.1, SW49.1, U1.15 (14/PB3)
col10: SW010.1, SW110.1, SW210.1, SW310.1, SW410.1, U1.16 (15/PB1)
col11: SW011.1, SW111.1, SW211.1, SW311.1, SW411.1, U1.17 (A0/PF7)
col12: SW012.1, SW112.1, SW212.1, SW312.1, SW412.1, U1.18 (A1/PF6)
col13: SW013.1, SW113.1, SW213.1, SW313.1, SW413.1, U1.19 (A2/PF5)
col14: SW014.1, SW114.1, SW214.1, SW314.1, SW414.1, U1.20 (A3/PF4)
row0: D00.1 (K), D01.1 (K), D02.1 (K), D03.1 (K), D04.1 (K), D05.1 (K), D06.1 (K), D07.1 (K), D08.1 (K), D09.1 (K), D010.1 (K), D011.1 (K), D012.1 (K), D013.1 (K), D014.1 (K), U1.25 (B7)
row1: D10.1 (K), D11.1 (K), D12.1 (K), D13.1 (K), D14.1 (K), D15.1 (K), D16.1 (K), D17.1 (K), D18.1 (K), D19.1 (K), D110.1 (K), D111.1 (K), D112.1 (K), D113.1 (K), D114.1 (K), U1.26 (D5)
row2: D20.1 (K), D21.1 (K), D22.1 (K), D23.1 (K), D24.1 (K), D25.1 (K), D26.1 (K), D27.1 (K), D28.1 (K), D29.1 (K), D210.1 (K), D211.1 (K), D212.1 (K), D213.1 (K), D214.1 (K), U1.27 (C7)
row3: D30.1 (K), D31.1 (K), D32.1 (K), D33.1 (K), D34.1 (K), D35.1 (K), D36.1 (K), D37.1 (K), D38.1 (K), D39.1 (K), D310.1 (K), D311.1 (K), D312.1 (K), D313.1 (K), D314.1 (K), U1.28 (F1)
row4: D40.1 (K), D41.1 (K), D42.1 (K), D43.1 (K), D44.1 (K), D45.1 (K), D46.1 (K), D47.1 (K), D48.1 (K), D49.1 (K), D410.1 (K), D411.1 (K), D412.1 (K), D413.1 (K), D414.1 (K), U1.29 (F0)
